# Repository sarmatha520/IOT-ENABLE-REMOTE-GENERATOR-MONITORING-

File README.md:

View this project on [CADLAB.io](https://cadlab.io/project/29314). 

# IOT-ENABLE-REMOTE-GENERATOR-MONITORING-

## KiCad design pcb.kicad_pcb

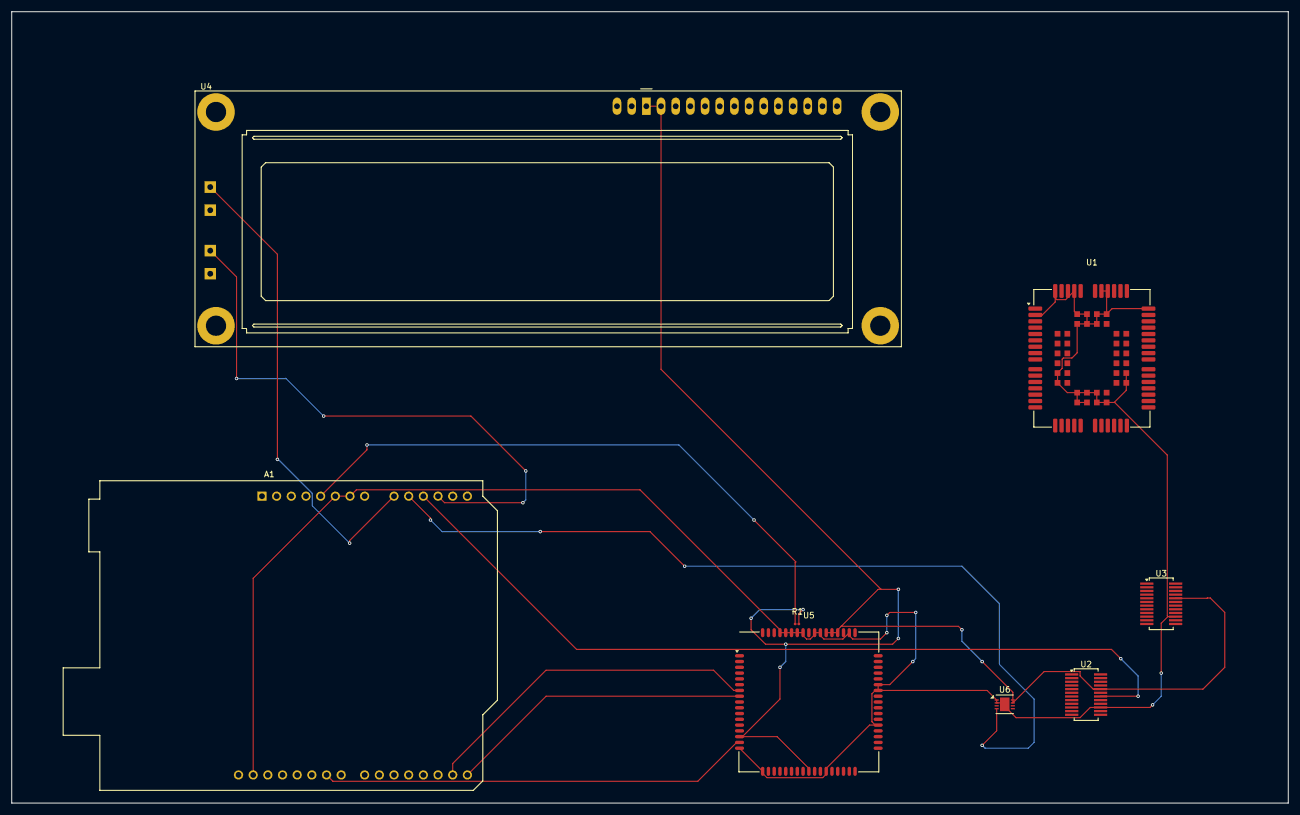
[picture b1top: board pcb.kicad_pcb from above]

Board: 2 copper layers, 221.0 x 137.0 mm, 8 parts (0 on the bottom side), 10 nets.

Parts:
A1: Arduino_UNO_R2
R1: R; R_0201_0603Metric
U1: BC95; Quectel_BC95
U2, U3: ACS709xLFTR-6BB; Allegro_QSOP-24_3.9x8.7mm_P0.635mm
U4: LCD-016N002L
U5: SIM900; SIMCom_SIM900
U6: LT3092xDD; DFN-8-1EP_3x3mm_P0.5mm_EP1.66x2.38mm

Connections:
GND: A1.6 (GND), A1.7 (GND), A1.29 (GND), U1.2 (GND), U1.43 (GND), U1.47 (GND), U1.48 (GND), U1.51 (GND), U1.52 (GND), U1.54 (GND), U1.59 (GND), U1.60 (GND), U1.61 (GND), U1.62 (GND), U1.63 (GND), U1.64 (GND), U1.65 (GND), U1.66 (GND), U1.71 (GND), U1.72 (GND), U1.73 (GND), U1.74 (GND), U1.81 (GND), U1.82 (GND), U1.83 (GND), U1.92 (GND), U1.93 (GND), U1.94 (GND), U2.15 (GND), U3.15 (GND), U5.17 (GND), U5.18 (GND), U5.29 (GND), U5.39 (GND), U5.45 (GND), U5.46 (GND), U5.53 (GND), U5.54 (GND), U5.58 (GND), U5.59 (GND), U5.61 (GND), U5.62 (GND), U5.63 (GND), U5.64 (GND), U5.65 (GND), U6.1, U6.2, U6.9
unnamed: A1.5 (+5V), R1.1
unnamed: A1.9 (A0), U4.A1
unnamed: A1.10 (A1), U6.4
unnamed: A1.11 (A2), U2.18 (VIOUT)
unnamed: A1.12 (A3), U4.A2
unnamed: A1.15 (D0/RX), U5.8 (RTS)
unnamed: A1.16 (D1/TX), U5.7 (CTS)
unnamed: A1.24 (D9), U5.16 (~RESET)
VCC: R1.2, U2.20 (VCC), U3.20 (VCC), U4.1 (VSS), U4.2 (VDD), U5.15 (VDD_EXT), U5.26 (VRTC), U5.55 (VBAT), U5.56 (VBAT), U5.57 (VBAT), U6.7, U6.8

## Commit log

2025-04-29 Backlink to CADLAB.io has been added.
